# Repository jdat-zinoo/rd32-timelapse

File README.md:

# rd32-timelapse

Toolchain setup on Ubuntu:
sudo apt install gcc-avr avr-libc avrdude

tool for makefile (make package?)

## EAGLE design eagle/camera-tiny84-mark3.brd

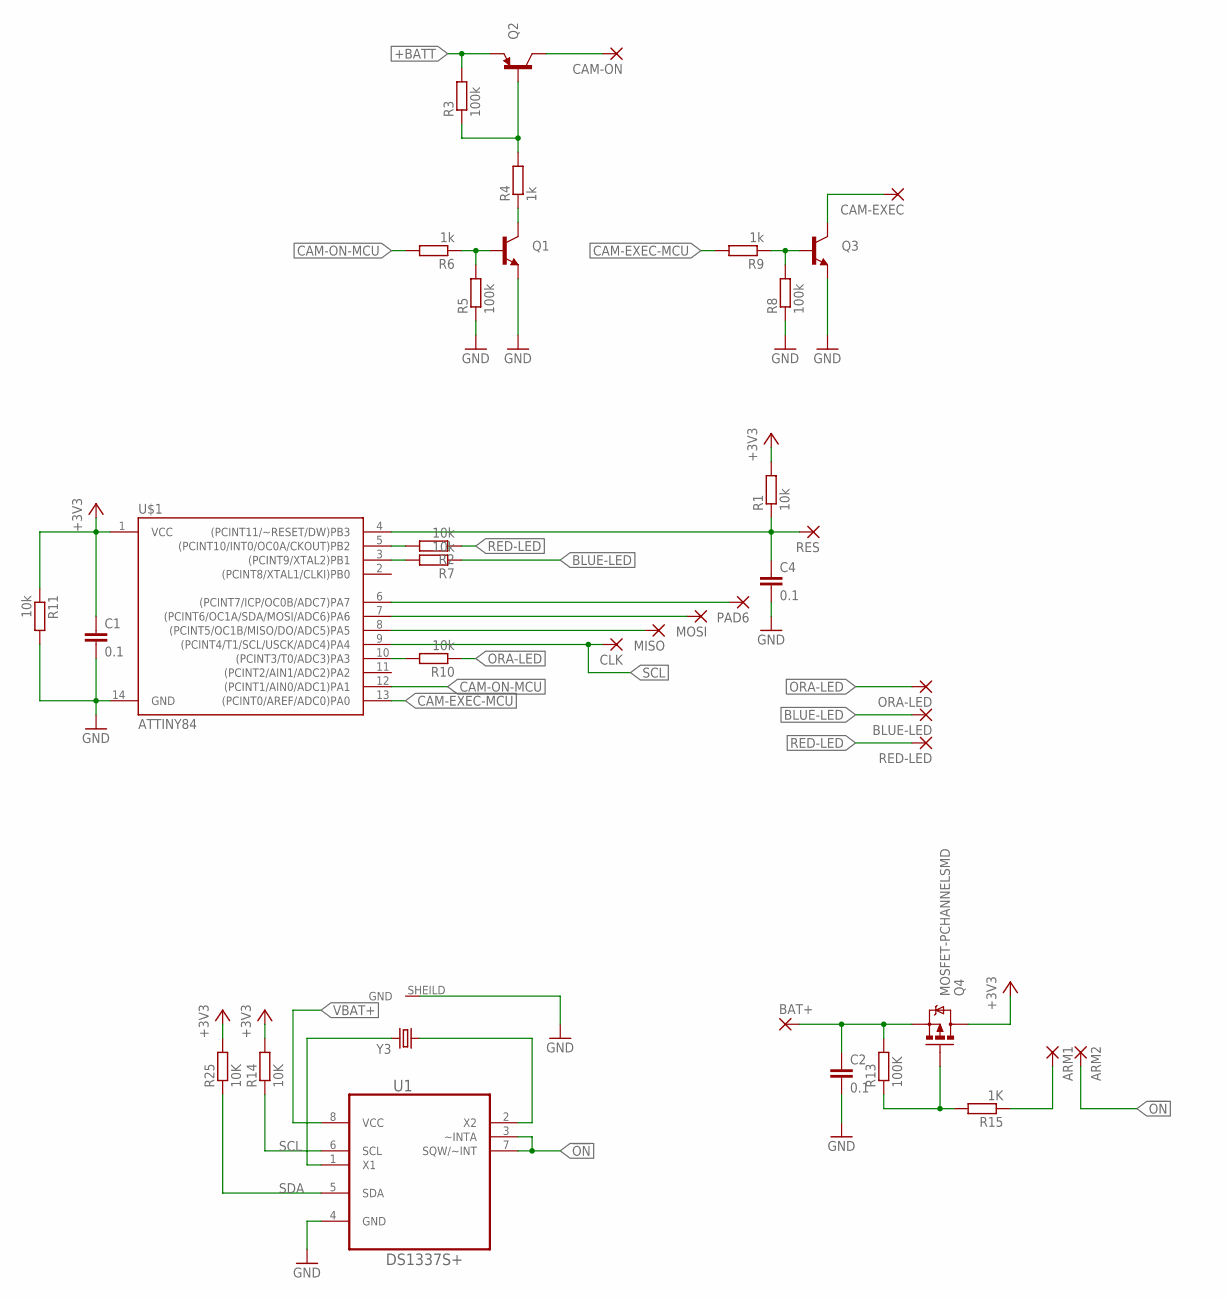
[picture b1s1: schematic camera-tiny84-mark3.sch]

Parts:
ARM1, ARM2: SMD2; SMD1,27-2,54
BAT+: SMD2; SMD1,27-2,54
BLUE-LED: SMD2; SMD1,27-2,54
C1, C2: 0.1; C0603
C4: 0.1; C1206
CAM-EXEC: SMD2; SMD1,27-2,54
CAM-ON: SMD2; SMD1,27-2,54
CLK: 1,6/0,8
MISO: 1,6/0,8
MOSI: 1,6/0,8
ORA-LED: SMD2; SMD1,27-2,54
PAD6: SMD2; SMD1,27-2,54
Q1, Q3: TRANSISTOR_NPNSOT23-3; SOT23-3
Q2: TRANSISTOR_PNPSMD; SOT23-3
Q4: MOSFET-PCHANNELSMD; SOT23-3
R1, R2, R7, R10, R11: 10k; R0603
R3, R5, R8: 100k; R0603
R4, R6, R9: 1k; R0603
R13: 100K; R0603
R14, R25: 10K; R0603
R15: 1K; R0603
RED-LED: SMD2; SMD1,27-2,54
RES: 1,6/0,8
U1: DS1337S+; SOIC127P600X175-8N
U$1: ATTINY84; SO14
Y3: CRYSTAL32-SMD_CRYSTAL32-SMD; CRYSTAL32-SMD_CRYSTAL-32KHZ-SMD

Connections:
!ON: ARM2.1, U1.3 (~INTA), U1.7 (SQW/~INT)
+3V3: C1.1, Q4.3 (D), R1.2, R11.1, R14.2, R25.2, U$1.1 (VCC)
+BATT: Q2.2 (E), R3.2
BLUE-LED: BLUE-LED.1, R7.1
CAM-EXEC-MCU: R9.2, U$1.13 ((PCINT0/AREF/ADC0)PA0)
CAM-ON-MCU: R6.2, U$1.12 ((PCINT1/AIN0/ADC1)PA1)
GND: C1.2, C2.2, C4.2, Q1.2 (E), Q3.2 (E), R5.1, R8.1, R11.2, U1.4 (GND), U$1.14 (GND), Y3.SHEILD (GND)
unnamed: MISO.1, U$1.8 ((PCINT5/OC1B/MISO/DO/ADC5)PA5)
unnamed: PAD6.1, U$1.6 ((PCINT7/ICP/OC0B/ADC7)PA7)
unnamed: C4.1, R1.1, RES.1, U$1.4 ((PCINT11/~RESET/DW)PB3)
unnamed: CAM-EXEC.1, Q3.3 (C)
unnamed: Q2.1 (B), R3.1, R4.2
unnamed: Q1.3 (C), R4.1
unnamed: Q1.1 (B), R5.2, R6.1
unnamed: Q3.1 (B), R8.2, R9.1
unnamed: CAM-ON.1, Q2.3 (C)
unnamed: Q4.1 (G), R13.1, R15.2
unnamed: ARM1.1, R15.1
unnamed: R2.2, U$1.5 ((PCINT10/INT0/OC0A/CKOUT)PB2)
unnamed: R7.2, U$1.3 ((PCINT9/XTAL2)PB1)
unnamed: R10.2, U$1.10 ((PCINT3/T0/ADC3)PA3)
unnamed: U1.2 (X2), Y3.X1 (1)
unnamed: U1.1 (X1), Y3.X2 (2)
ORA-LED: ORA-LED.1, R10.1
RED-LED: R2.1, RED-LED.1
SCL: CLK.1, R14.1, U1.6 (SCL), U$1.9 ((PCINT4/T1/SCL/USCK/ADC4)PA4)
SDA: MOSI.1, R25.1, U1.5 (SDA), U$1.7 ((PCINT6/OC1A/SDA/MOSI/ADC6)PA6)
VBAT+: BAT+.1, C2.1, Q4.2 (S), R13.2, U1.8 (VCC)

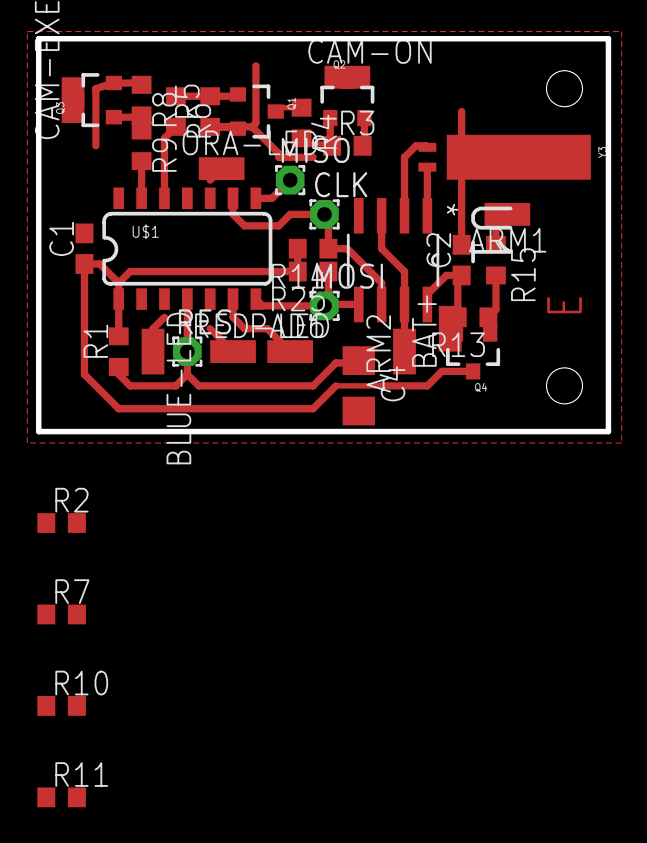
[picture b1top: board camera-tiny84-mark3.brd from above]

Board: 2 copper layers, 31.6 x 21.8 mm, 38 parts (0 on the bottom side), 28 nets.

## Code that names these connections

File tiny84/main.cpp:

#define timeLapseMinutes 3

#define errCount 8
#include <stdbool.h>
#include <stdlib.h>
#include <inttypes.h>
#include <stdint.h>

#include <avr/io.h>
#include <avr/interrupt.h>
#include <util/delay.h>
#include <avr/sleep.h>
#include <avr/eeprom.h>

#include "dbg_putchar.h"

#include "pins.hh"

#include "rtc.h" 

#define t0presc0	1
#define t0presc8	2
#define t0presc64	3
#define t0presc256	4
#define t0presc1024	5

#define int0Low 0
#define int0Change 1
#define int0Fall 2
#define int0Rise 3

#define stateOff 0
#define stateVideo 1
#define stateFoto 2
#define stateMdVideo 3
#define stateMdFoto 4
#define stateUSB 5
#define stateError 6
#define stateRecording 7
#define stateTV 8
#define stateUnknown 9

/*
PA0 - play/exec button (OUT)
PA1 - Power button (OUT)
PA2 -
PA3 - Serial debug out
PA4 - I2C clock (ISP)
PA5 - (ISP)
PA6 - I2C data (ISP)
PA7 - BLUE led (IN)

PB0 - 
PB1 - Orange led (IN)
PB2 - RED led (IN)
PB3 - reset (ISP)
*/


DigitalOut<PortA::pin0> execPin;
DigitalOut<PortA::pin1> powerPin;

DigitalIn<PortA::pin7> redLed;
DigitalIn<PortB::pin8> blueLed;
DigitalIn<PortB::pin9> orangeLed;

volatile uint8_t cnt=0;
volatile uint8_t oldcnt=0;
volatile uint8_t blink=0;


uint8_t isMotion(){
    return orangeLed.read() ? 1 : 0;
}

uint8_t isFoto(){
    return redLed.read() ? 1 : 0;
}

uint8_t isVideo(){
    return blueLed.read() ? 1 : 0;
}


uint8_t bl=0;	

uint8_t cameraState(){

    
    if (isMotion() && isFoto()) return stateMdFoto;
    if (isMotion() && isVideo()) return stateMdVideo;
    if (isFoto() && isVideo()) return stateTV;
    if (isFoto()) return stateFoto;
    blink=0;
    _delay_ms(1500);
	bl=blink;
	
    
    //dbg_putchar('S');
    
    //dbg_putchar(bl);
	if ((bl>0x08) && (bl<0x18)) //error, blue fast blink
	{
        //dbg_putchar(bl);
		return stateError;
	}
	else if ((bl>0x38) && (bl<0x48)) //recording, blue slow blink
	{
		return stateRecording;
	}
    else {                
        if (isVideo()) return stateVideo;        
    }
	return stateOff;	
}


// delay 4500
void turnCameraOff(){
	powerPin.high();
	_delay_ms(4000);
	powerPin.low();
	_delay_ms(500);
}

// delay 2250
void turnOnCamera(){
	powerPin.high();
	_delay_ms(750);
	powerPin.low();
	_delay_ms(1500);
}

// delay 1500
void modeButton(){
	powerPin.high();
	_delay_ms(750);
	powerPin.low();
	_delay_ms(750);
}
// delay1500
void execButton(){
	execPin.high();
	_delay_ms(500);
	execPin.low();
	_delay_ms(500);
}

uint8_t errCnt=0;

int main()
{
	
	//dbg_tx_init();
	//dbg_putchar('\n');
    
	TCCR0B |=t0presc64;
	TIFR0 |= 0x01;
	TIMSK0 |= 0x01;
	
	MCUCR |=int0Change;
	GIMSK |=1<<6;
	
	sei();
	
	ADCSRA &= ~(1<<ADEN);	//disable ADC
    
    
    uint8_t a;
    errCnt=0;

    rtcInit();        
    turnOnCamera();
    _delay_ms(3000);
    blink=0;
    modeButton();
    
    _delay_ms(250); //compensation for precise RTC
    rtcSetAlarm(timeLapseMinutes);    	
    while(1){
		a=cameraState();
		//dbg_putchar(a+0x30);
        //dbg_putchar(errCnt+0x30);
		//dbg_putchar('\n');
		switch (a){
			case stateError:
                errCnt++;
                //dbg_putchar('e');
				break;		
			case stateRecording:
                //dbg_putchar('R');
                execButton();
				break;
			case stateOff:
                //dbg_putchar('o');
                turnOnCamera();
                break;
			case stateFoto:
                //dbg_putchar('f');
                errCnt++;
                _delay_ms(500);
                execButton();
                _delay_ms(3500);
                turnCameraOff();
                //dbg_putchar('\n');
                errCnt=9;
				break;
			case stateMdVideo:
                //dbg_putchar('V');                
                modeButton();
                errCnt++;
                if (errCnt>=errCount) break;
				break;
			case stateMdFoto:
                //dbg_putchar('F');
                modeButton();
                errCnt++;
                if (errCnt>=errCount) break;
				break;
			case stateVideo:
                //dbg_putchar('v');
                //while (isVideo()){
                    modeButton();
                    errCnt++;
                    if (errCnt>=errCount) break;
                //}
                break;
			default:
                //dbg_putchar('W');
				break;
		}
        if (errCnt>=errCount){
            rtcTurnOff();
        }
	}
	
}

ISR ( TIM0_OVF_vect ) { cnt++; }

ISR(EXT_INT0_vect){
	blink=cnt-oldcnt;
	oldcnt=cnt;
}

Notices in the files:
parts and their libraries:
SparkFun-DigitalIC: Licensing: Creative Commons ShareAlike 4.0 International - https://creativecommons.org/licenses/by-sa/4.0
